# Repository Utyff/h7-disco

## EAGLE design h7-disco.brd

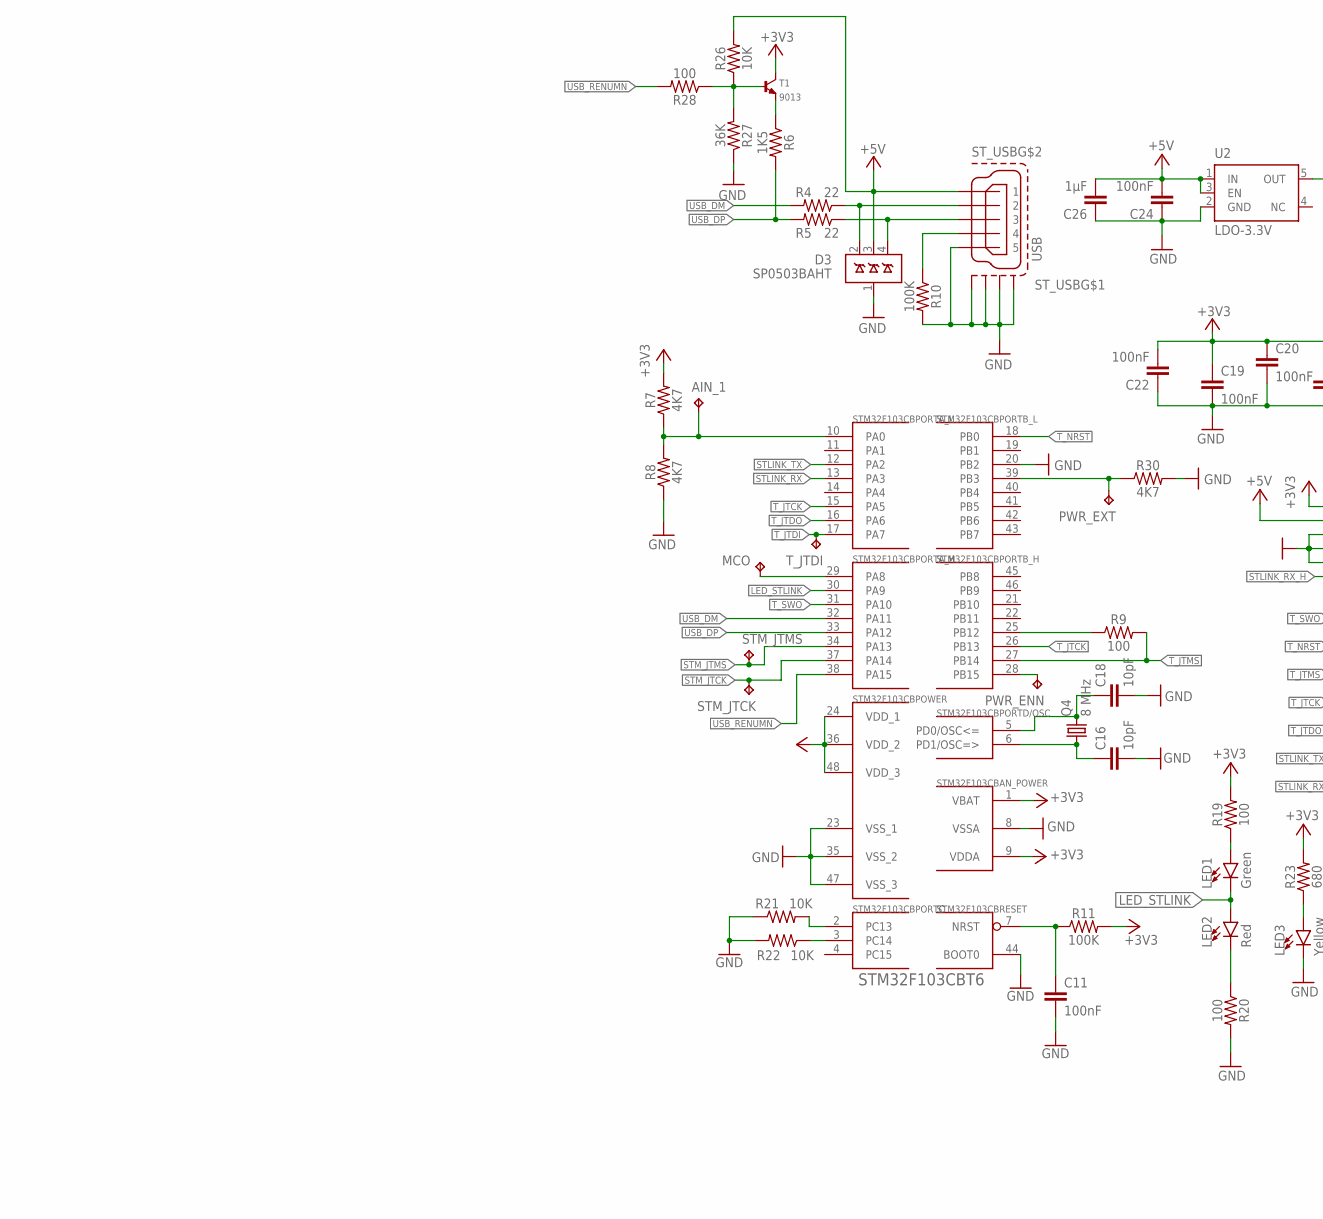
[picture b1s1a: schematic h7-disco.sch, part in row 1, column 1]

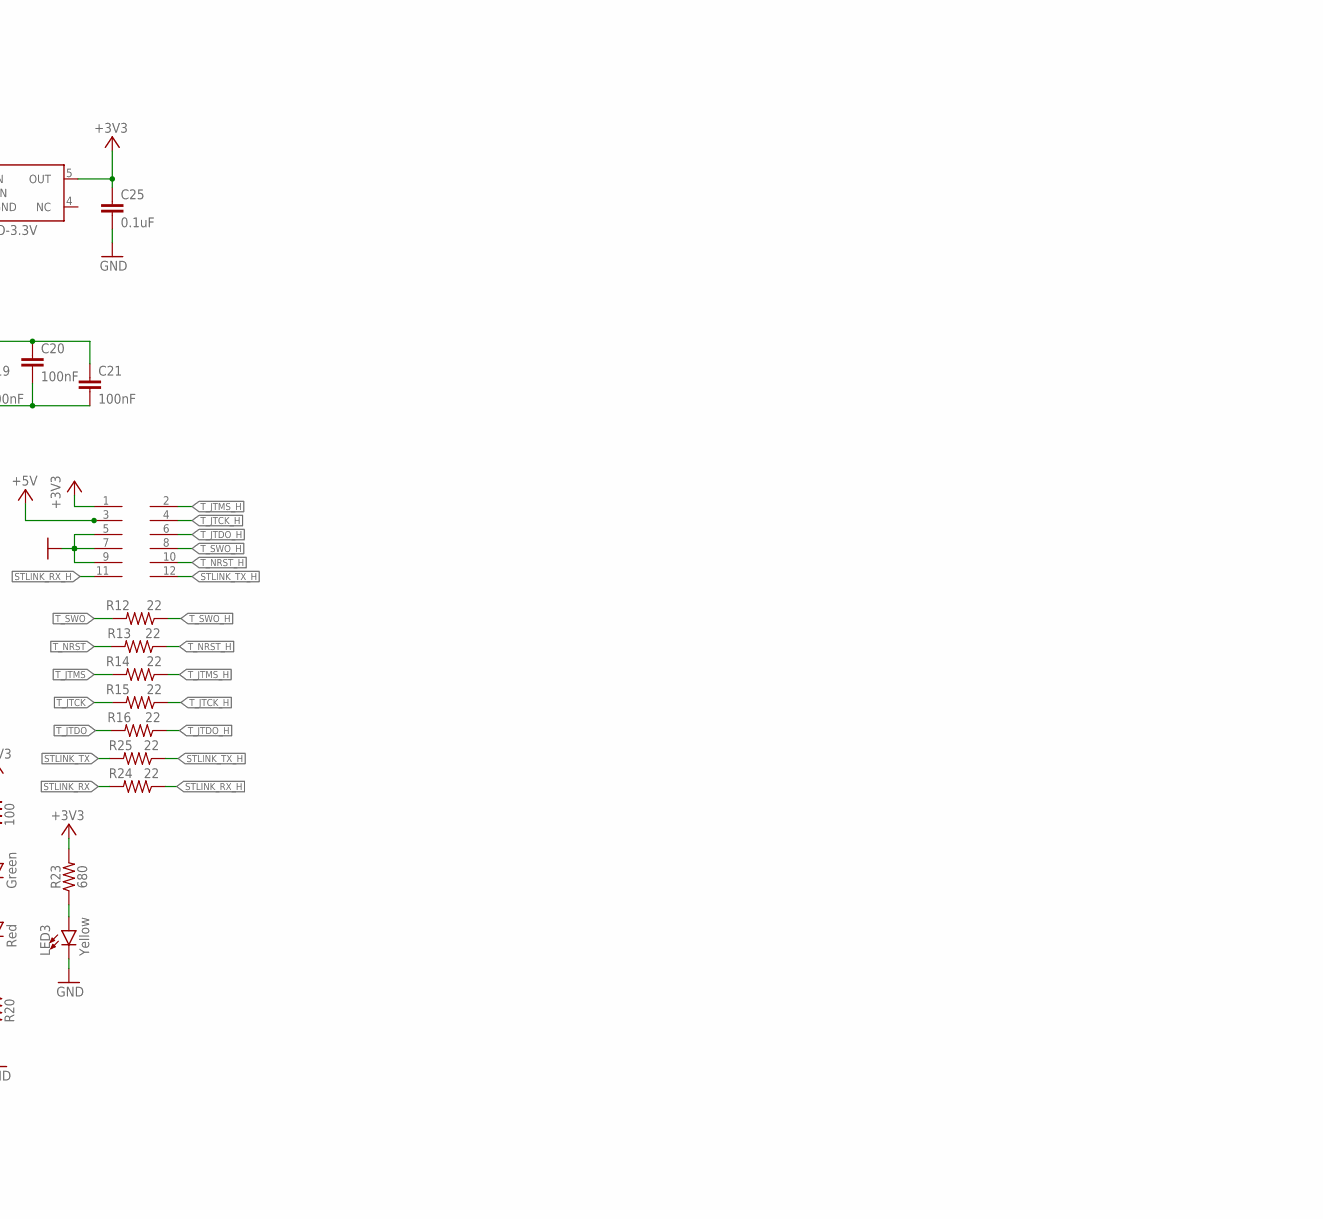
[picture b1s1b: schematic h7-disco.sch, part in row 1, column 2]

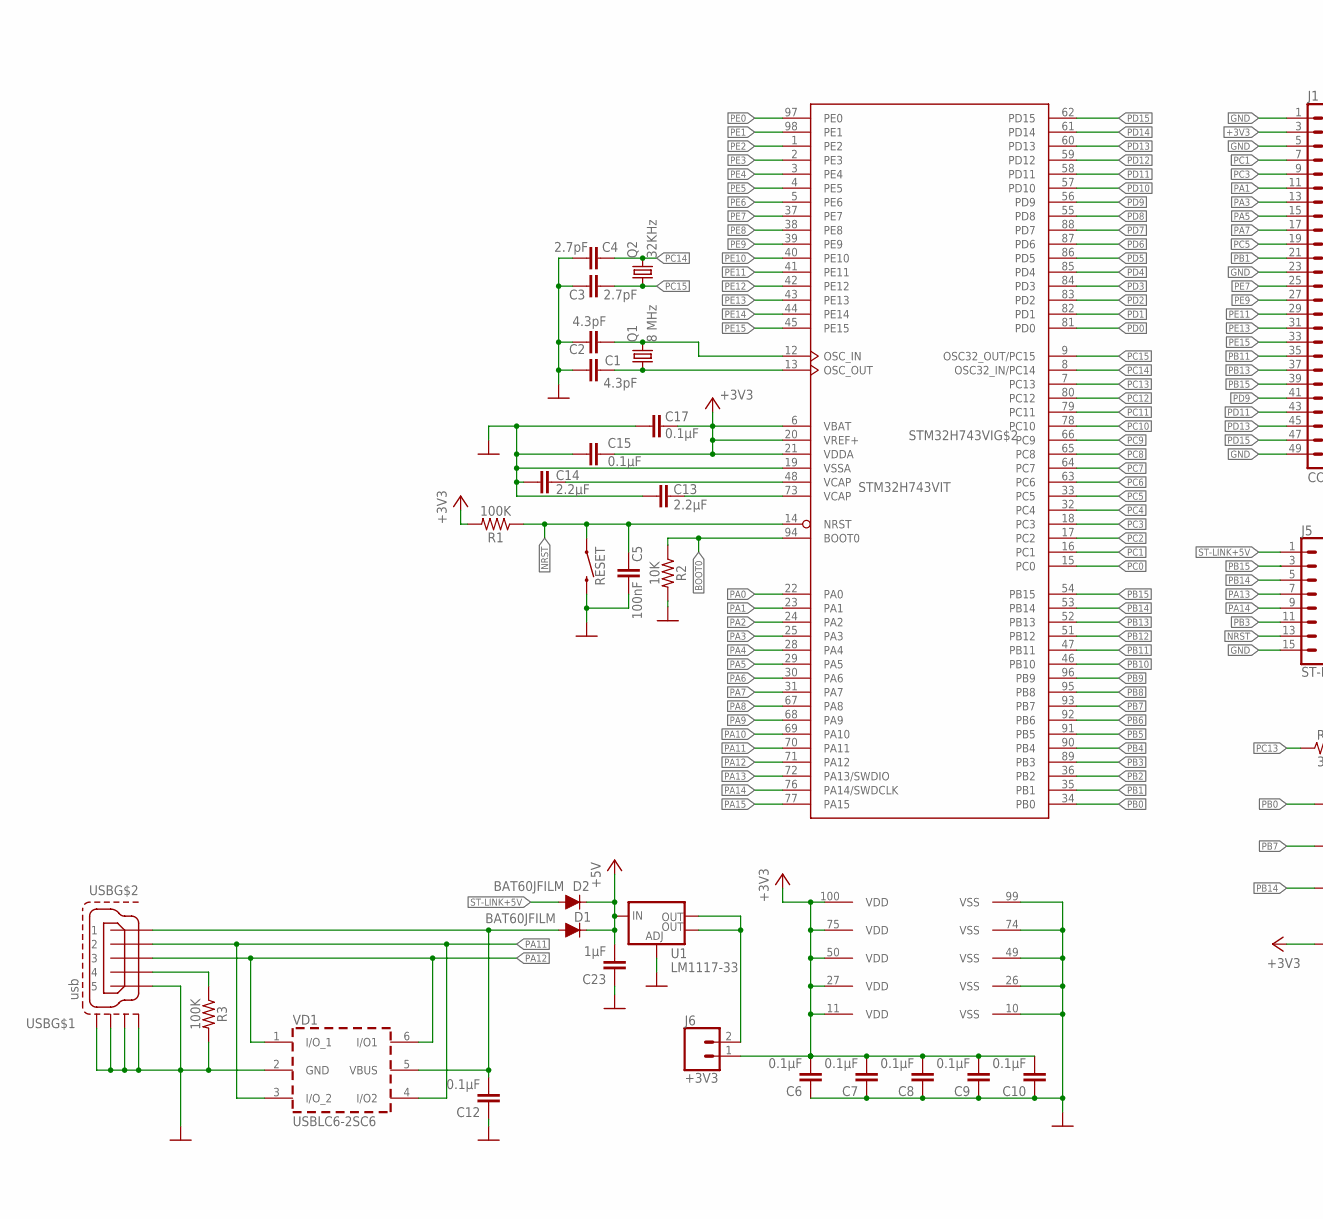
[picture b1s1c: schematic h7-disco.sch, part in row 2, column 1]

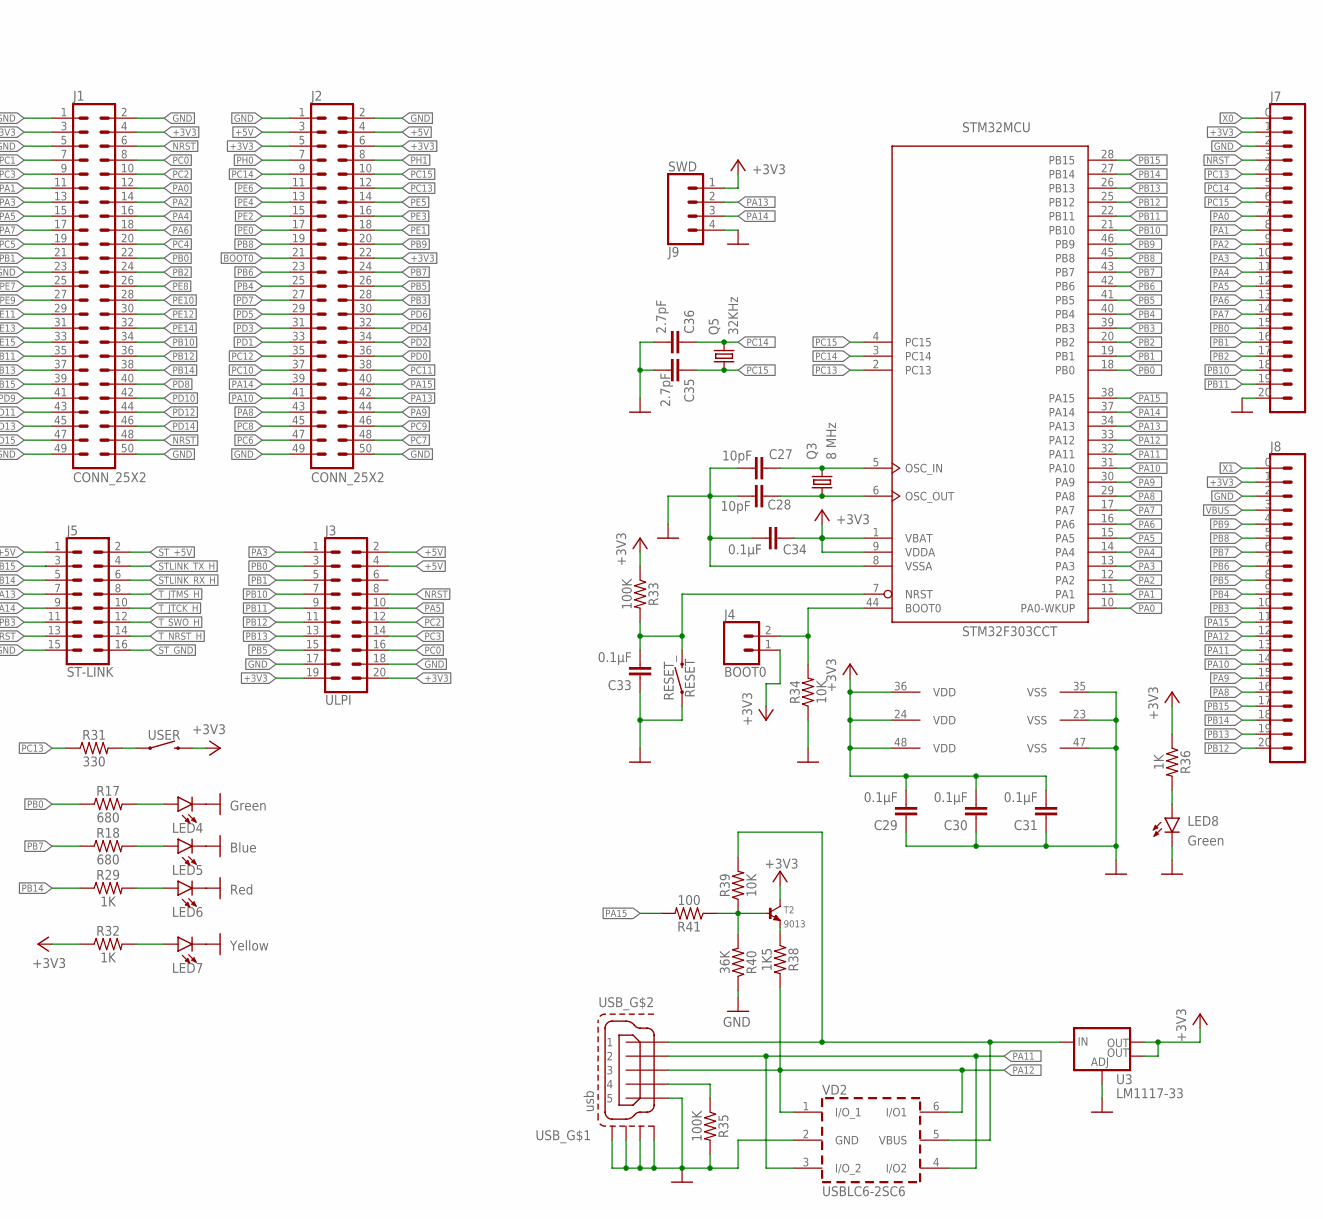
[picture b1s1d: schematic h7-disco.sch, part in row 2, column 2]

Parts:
AIN_1: TPTP10R; TP10R
C1, C2: 4.3pF; 0805
C3, C4, C35, C36: 2.7pF; 0805
C5, C11, C19, C20, C21, C22, C24: 100nF; 0805
C6, C7, C8, C9, C10, C12, C15, C17, C29, C30, C31, C33, C34: 0.1µF; 0805
C13, C14: 2.2µF; 0805
C16, C18, C27, C28: 10pF; 0805
C23, C26: 1µF; 1206
C25: 0.1uF; 0805
CN2: M06X2; PLANAR-6X2
D1, D2: BAT60JFILM; SOD-323
D3: SP0503BAHT; SOT143
J1, J2: CONN_25X2; 2X25
J3: ULPI; 2X10-MIRROR
J4: BOOT0; 1X02
J5: ST-LINK; 2X8
J6: +3V3; 1X02
J7, J8: CONN_21; 1X21
J9: SWD; 1X04
LED1, LED4, LED8: Green; LED-0805
LED2, LED6: Red; LED-0805
LED3, LED7: Yellow; LED-0805
LED5: Blue; LED-0805
MCO: TPTP10R; TP10R
PWR_ENN: TPTP10R; TP10R
PWR_EXT: TPTP10R; TP10R
Q1, Q3, Q4: 8 MHz; HC49/S
Q2, Q5: 32KHz; TC26H
R1, R3, R10, R11, R33, R35: 100K; 0805
R2, R21, R22, R26, R34, R39: 10K; 0805
R4, R5, R12, R13, R14, R15, R16, R24, R25: 22; 0805
R6, R38: 1K5; 0805
R7, R8, R30: 4K7; 0805
R9, R19, R20, R28, R41: 100; 0805
R17, R18, R23: 680; 0805
R27, R40: 36K; 0805
R29, R32, R36: 1K; 0805
R31: 330; 0805
RESET: MOMENTARY-SWITCH-SPST-SMD-6.2MM-TALL; TACTILE_SWITCH_SMD_6.2MM_TALL
RESET_: RESET; TACTILE_SWITCH_SMD_6.0X3.5MM
STM32: STM32F303CCT; LQFP48
STM32F103CB: STM32F103CBT6; TQFP48
STM32H743VI: STM32H743VIT; LQFP100
STM_JTCK: TPTP10R; TP10R
STM_JTMS: TPTP10R; TP10R
ST_USB: USB; MICRO_USB-B_4.85_HORN
T1, T2: 9013; SOT-23
T_JTDI: TPTP10R; TP10R
U1, U3: LM1117-33; SOT223
U2: LDO-3.3V; SOT23-5
USB: usb; MICRO_USB-B_4.85_HORN
USB_: usb; MICRO_USB-B_4.85_HORN
USER: MOMENTARY-SWITCH-SPST-SMD-6.2MM-TALL; TACTILE_SWITCH_SMD_6.2MM_TALL
VD1, VD2: USBLC6-2SC6; SOT-23-6L

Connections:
+3V3: C6.2, C7.2, C8.2, C9.2, C10.2, C15.1, C17.1, C29.2, C30.2, C31.2, C34.1, J1.3, J1.4, J2.5, J2.6, J2.22, J3.19, J3.20, J4.1, J6.1, J7.1, J8.1, J9.1, R1.2, R32.1, R33.1, R36.1, STM32.1 (VBAT), STM32.9 (VDDA), STM32.24 (VDD), STM32.36 (VDD), STM32.48 (VDD), STM32H743VI.6 (VBAT), STM32H743VI.11 (VDD), STM32H743VI.20 (VREF+), STM32H743VI.21 (VDDA), STM32H743VI.27 (VDD), STM32H743VI.50 (VDD), STM32H743VI.75 (VDD), STM32H743VI.100 (VDD), T2.3 (C), U3.2 (OUT), U3.4 (OUT), USER.B2 (2)
+5V: C23.2, D1.C, D2.C, J2.3, J2.4, J3.2, J3.4, U1.3 (IN)
AIN_1: AIN_1.TP, R7.1, R8.2, STM32F103CB.10 (PA0)
BOOT0: J2.21, R2.1, STM32H743VI.94 (BOOT0)
BOOT0_: J4.2, R34.2, STM32.44 (BOOT0)
D+1: D3.4 (D3), R5.1, ST_USB.3
D-1: D3.2 (D1), R4.1, ST_USB.2
GND: C1.1, C2.1, C3.1, C4.1, C5.1, C6.1, C7.1, C8.1, C9.1, C10.1, C12.1, C13.2, C14.2, C15.2, C17.2, C23.1, C27.1, C28.2, C29.1, C30.1, C31.1, C33.1, C34.2, C35.1, C36.1, J1.1, J1.2, J1.5, J1.23, J1.49, J1.50, J2.1, J2.2, J2.49, J2.50, J3.17, J3.18, J5.15, J7.2, J7.20, J8.2, J9.4, LED4.C, LED5.C, LED6.C, LED7.C, LED8.C, R2.2, R3.2, R34.1, R35.2, R40.1, RESET.B2 (2), RESET_.1, STM32.8 (VSSA), STM32.23 (VSS), STM32.35 (VSS), STM32.47 (VSS), STM32H743VI.10 (VSS), STM32H743VI.19 (VSSA), STM32H743VI.26 (VSS), STM32H743VI.49 (VSS), STM32H743VI.74 (VSS), STM32H743VI.99 (VSS), U1.1 (ADJ), U3.1 (ADJ), USB.5, USB.M1 (S1), USB.M2 (S2), USB.M3 (S3), USB.M4 (S4), USB_.5, USB_.M1 (S1), USB_.M2 (S2), USB_.M3 (S3), USB_.M4 (S4), VD1.2 (GND), VD2.2 (GND)
ID: R3.1, USB.4
ID_: R35.1, USB_.4
LED_STLINK: LED1.C, LED2.A, STM32F103CB.30 (PA9)
MCO: MCO.TP, STM32F103CB.29 (PA8)
unnamed: C1.2, Q1.1, STM32H743VI.13 (OSC_OUT)
unnamed: C2.2, Q1.2, STM32H743VI.12 (OSC_IN)
unnamed: C11.1, R11.1, STM32F103CB.7 (NRST)
unnamed: C18.1, Q4.2, STM32F103CB.5 (PD0/OSC<=)
unnamed: C16.1, Q4.1, STM32F103CB.6 (PD1/OSC=>)
unnamed: R26.1, R27.2, R28.1, T1.1 (B)
unnamed: LED2.C, R20.1
unnamed: LED1.A, R19.1
unnamed: LED5.A, R18.2
unnamed: J6.2, U1.2 (OUT), U1.4 (OUT)
unnamed: LED3.A, R23.1
unnamed: R6.1, T1.2 (E)
unnamed: LED4.A, R17.2
unnamed: R21.2, STM32F103CB.2 (PC13)
unnamed: R22.1, STM32F103CB.3 (PC14)
unnamed: LED7.A, R32.2
unnamed: R10.1, ST_USB.4
unnamed: R38.1, T2.2 (E)
unnamed: R39.1, R40.2, R41.1, T2.1 (B)
unnamed: LED6.A, R29.2
unnamed: R31.2, USER.A2 (1)
unnamed: LED8.A, R36.2
NRST: C5.2, J1.6, J1.48, J3.8, J5.13, R1.1, RESET.A2 (1), STM32H743VI.14 (NRST)
NRST_: C33.2, J7.3, R33.2, RESET_.2, STM32.7 (NRST)
PA0: J1.12, STM32H743VI.22 (PA0)
PA0_: J7.7, STM32.10 (PA0-WKUP)
PA1: J1.11, STM32H743VI.23 (PA1)
PA1_: J7.8, STM32.11 (PA1)
PA2: J1.14, STM32H743VI.24 (PA2)
PA2_: J7.9, STM32.12 (PA2)
PA3: J1.13, J3.1, STM32H743VI.25 (PA3)
PA3_: J7.10, STM32.13 (PA3)
PA4: J1.16, STM32H743VI.28 (PA4)
PA4_: J7.11, STM32.14 (PA4)
PA5: J1.15, J3.10, STM32H743VI.29 (PA5)
PA5_: J7.12, STM32.15 (PA5)
PA6: J1.18, STM32H743VI.30 (PA6)
PA6_: J7.13, STM32.16 (PA6)
PA7: J1.17, STM32H743VI.31 (PA7)
PA7_: J7.14, STM32.17 (PA7)
PA8: J2.43, STM32H743VI.67 (PA8)
PA8_: J8.16, STM32.29 (PA8)
PA9: J2.44, STM32H743VI.68 (PA9)
PA9_: J8.15, STM32.30 (PA9)
PA10: J2.41, STM32H743VI.69 (PA10)
PA10_: J8.14, STM32.31 (PA10)
PA11: STM32H743VI.70 (PA11), USB.2, VD1.3 (I/O_2), VD1.4 (I/O2)
PA11_: J8.13, STM32.32 (PA11), USB_.2, VD2.3 (I/O_2), VD2.4 (I/O2)
PA12: STM32H743VI.71 (PA12), USB.3, VD1.1 (I/O_1), VD1.6 (I/O1)
PA12_: J8.12, R38.2, STM32.33 (PA12), USB_.3, VD2.1 (I/O_1), VD2.6 (I/O1)
PA13: J2.42, J5.7, STM32H743VI.72 (PA13/SWDIO)
PA13_: J9.2, STM32.34 (PA13)
PA14: J2.39, J5.9, STM32H743VI.76 (PA14/SWDCLK)
PA14_: J9.3, STM32.37 (PA14)
PA15: J2.40, STM32H743VI.77 (PA15)
PA15_: J8.11, R41.2, STM32.38 (PA15)
PB0: J1.22, J3.3, R17.1, STM32H743VI.34 (PB0)
PB0_: J7.15, STM32.18 (PB0)
PB1: J1.21, J3.5, STM32H743VI.35 (PB1)
PB1_: J7.16, STM32.19 (PB1)
PB2: J1.24, STM32H743VI.36 (PB2)
PB2_: J7.17, STM32.20 (PB2)
PB3: J2.28, J5.11, STM32H743VI.89 (PB3)
PB3_: J8.10, STM32.39 (PB3)
PB4: J2.25, STM32H743VI.90 (PB4)
PB4_: J8.9, STM32.40 (PB4)
PB5: J2.26, J3.15, STM32H743VI.91 (PB5)
PB5_: J8.8, STM32.41 (PB5)
PB6: J2.23, STM32H743VI.92 (PB6)
PB6_: J8.7, STM32.42 (PB6)
PB7: J2.24, R18.1, STM32H743VI.93 (PB7)
PB7_: J8.6, STM32.43 (PB7)
PB8: J2.19, STM32H743VI.95 (PB8)
PB8_: J8.5, STM32.45 (PB8)
PB9: J2.20, STM32H743VI.96 (PB9)
PB9_: J8.4, STM32.46 (PB9)
PB10: J1.34, J3.7, STM32H743VI.46 (PB10)
PB10_: J7.18, STM32.21 (PB10)
PB11: J1.35, J3.9, STM32H743VI.47 (PB11)
PB11_: J7.19, STM32.22 (PB11)
PB12: J1.36, J3.11, STM32H743VI.51 (PB12)
PB12_: J8.20, STM32.25 (PB12)
PB13: J1.37, J3.13, STM32H743VI.52 (PB13)
PB13_: J8.19, STM32.26 (PB13)
PB14: J1.38, J5.5, R29.1, STM32H743VI.53 (PB14)
PB14_: J8.18, STM32.27 (PB14)
PB15: J1.39, J5.3, STM32H743VI.54 (PB15)
PB15_: J8.17, STM32.28 (PB15)
PB16: PWR_ENN.TP, STM32F103CB.28 (PB15)
PC0: J1.8, J3.16, STM32H743VI.15 (PC0)
PC1: J1.7, STM32H743VI.16 (PC1)
PC2: J1.10, J3.12, STM32H743VI.17 (PC2)
PC3: J1.9, J3.14, STM32H743VI.18 (PC3)
PC4: J1.20, STM32H743VI.32 (PC4)
PC5: J1.19, STM32H743VI.33 (PC5)
PC6: J2.47, STM32H743VI.63 (PC6)
PC7: J2.48, STM32H743VI.64 (PC7)
PC8: J2.45, STM32H743VI.65 (PC8)
PC9: J2.46, STM32H743VI.66 (PC9)
PC10: J2.37, STM32H743VI.78 (PC10)
PC11: J2.38, STM32H743VI.79 (PC11)
PC12: J2.35, STM32H743VI.80 (PC12)
PC13: J2.12, R31.1, STM32H743VI.7 (PC13)
PC13_: J7.4, STM32.2 (PC13)
PC14: C4.2, J2.9, Q2.2, STM32H743VI.8 (OSC32_IN/PC14)
PC14_: C36.2, J7.5, Q5.2, STM32.3 (PC14)
PC15: C3.2, J2.10, Q2.1, STM32H743VI.9 (OSC32_OUT/PC15)
PC15_: C35.2, J7.6, Q5.1, STM32.4 (PC15)
PD0: J2.36, STM32H743VI.81 (PD0)
PD1: J2.33, STM32H743VI.82 (PD1)
PD2: J2.34, STM32H743VI.83 (PD2)
PD3: J2.31, STM32H743VI.84 (PD3)
PD4: J2.32, STM32H743VI.85 (PD4)
PD5: J2.29, STM32H743VI.86 (PD5)
PD6: J2.30, STM32H743VI.87 (PD6)
PD7: J2.27, STM32H743VI.88 (PD7)
PD8: J1.40, STM32H743VI.55 (PD8)
PD9: J1.41, STM32H743VI.56 (PD9)
PD10: J1.42, STM32H743VI.57 (PD10)
PD11: J1.43, STM32H743VI.58 (PD11)
PD12: J1.44, STM32H743VI.59 (PD12)
PD13: J1.45, STM32H743VI.60 (PD13)
PD14: J1.46, STM32H743VI.61 (PD14)
PD15: J1.47, STM32H743VI.62 (PD15)
PE0: J2.17, STM32H743VI.97 (PE0)
PE1: J2.18, STM32H743VI.98 (PE1)
PE2: J2.15, STM32H743VI.1 (PE2)
PE3: J2.16, STM32H743VI.2 (PE3)
PE4: J2.13, STM32H743VI.3 (PE4)
PE5: J2.14, STM32H743VI.4 (PE5)
PE6: J2.11, STM32H743VI.5 (PE6)
PE7: J1.25, STM32H743VI.37 (PE7)
PE8: J1.26, STM32H743VI.38 (PE8)
PE9: J1.27, STM32H743VI.39 (PE9)
PE10: J1.28, STM32H743VI.40 (PE10)
PE11: J1.29, STM32H743VI.41 (PE11)
PE12: J1.30, STM32H743VI.42 (PE12)
PE13: J1.31, STM32H743VI.43 (PE13)
PE14: J1.32, STM32H743VI.44 (PE14)
PE15: J1.33, STM32H743VI.45 (PE15)
PF0_: C27.2, Q3.2, STM32.5 (OSC_IN)
PF1_: C28.1, Q3.1, STM32.6 (OSC_OUT)
PH0: J2.7
PH1: J2.8
PWR_EXT: PWR_EXT.TP, R30.1, STM32F103CB.39 (PB3)
ST-LINK+5V: D2.A, J5.1
STLINK_RX: R24.2, STM32F103CB.13 (PA3)
STLINK_RX_H: CN2.11, J5.6, R24.1
STLINK_TX: R25.2, STM32F103CB.12 (PA2)
STLINK_TX_H: CN2.12, J5.4, R25.1
STM_JTCK: STM32F103CB.37 (PA14), STM_JTCK.TP
STM_JTMS: STM32F103CB.34 (PA13), STM_JTMS.TP
ST_+3V3: C19.1, C20.1, C21.1, C22.2, C25.1, CN2.1, R7.2, R11.2, R19.2, R23.2, STM32F103CB.1 (VBAT), STM32F103CB.9 (VDDA), STM32F103CB.24 (VDD_1), STM32F103CB.36 (VDD_2), STM32F103CB.48 (VDD_3), T1.3 (C), U2.5 (OUT)
ST_+5V: C24.2, C26.2, CN2.3, D3.3 (D2), J5.2, R26.2, ST_USB.1, U2.1 (IN), U2.3 (EN)
ST_GND: C11.2, C16.2, C18.2, C19.2, C20.2, C21.2, C22.1, C24.1, C25.2, C26.1, CN2.5, CN2.7, CN2.9, D3.1 (GND), J5.16, LED3.C, R8.1, R10.2, R20.2, R21.1, R22.2, R27.1, R30.2, STM32F103CB.8 (VSSA), STM32F103CB.20 (PB2), STM32F103CB.23 (VSS_1), STM32F103CB.35 (VSS_2), STM32F103CB.44 (BOOT0), STM32F103CB.47 (VSS_3), ST_USB.5, ST_USB.M1 (S1), ST_USB.M2 (S2), ST_USB.M3 (S3), ST_USB.M4 (S4), U2.2 (GND)
T_JTCK: R15.2, STM32F103CB.15 (PA5), STM32F103CB.26 (PB13)
T_JTCK_H: CN2.4, J5.10, R15.1
T_JTDI: STM32F103CB.17 (PA7), T_JTDI.TP
T_JTDO: R16.2, STM32F103CB.16 (PA6)
T_JTDO_H: CN2.6, R16.1
T_JTMS: R9.2, R14.2, STM32F103CB.27 (PB14)
T_JTMS_H: CN2.2, J5.8, R14.1
T_NRST: R13.2, STM32F103CB.18 (PB0)
T_NRST_H: CN2.10, J5.14, R13.1
T_SWDIO_IN: R9.1, STM32F103CB.25 (PB12)
T_SWO: R12.2, STM32F103CB.31 (PA10)
T_SWO_H: CN2.8, J5.12, R12.1
USB_DM: R4.2, STM32F103CB.32 (PA11)
USB_DP: R5.2, R6.2, STM32F103CB.33 (PA12)
USB_RENUMN: R28.2, STM32F103CB.38 (PA15)
VBUS: C12.2, D1.A, USB.1, VD1.5 (VBUS)
VBUS_: J8.3, R39.2, U3.3 (IN), USB_.1, VD2.5 (VBUS)
VCAP1: C14.1, STM32H743VI.48 (VCAP)
VCAP2: C13.1, STM32H743VI.73 (VCAP)
X0: J7.0
X1: J8.0

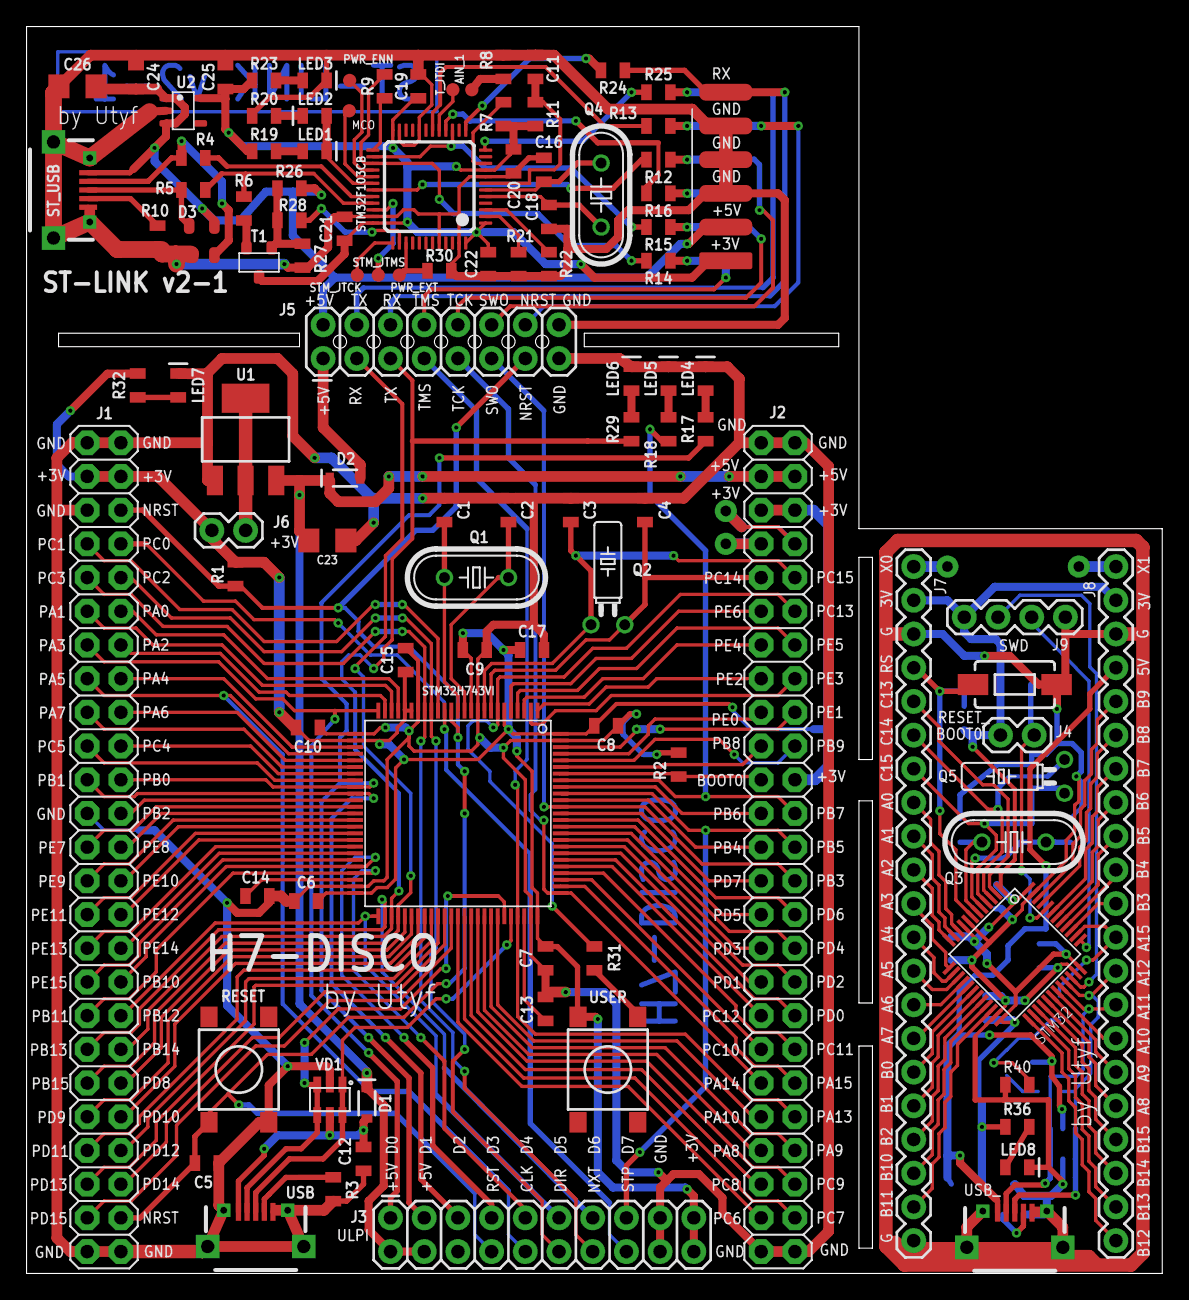
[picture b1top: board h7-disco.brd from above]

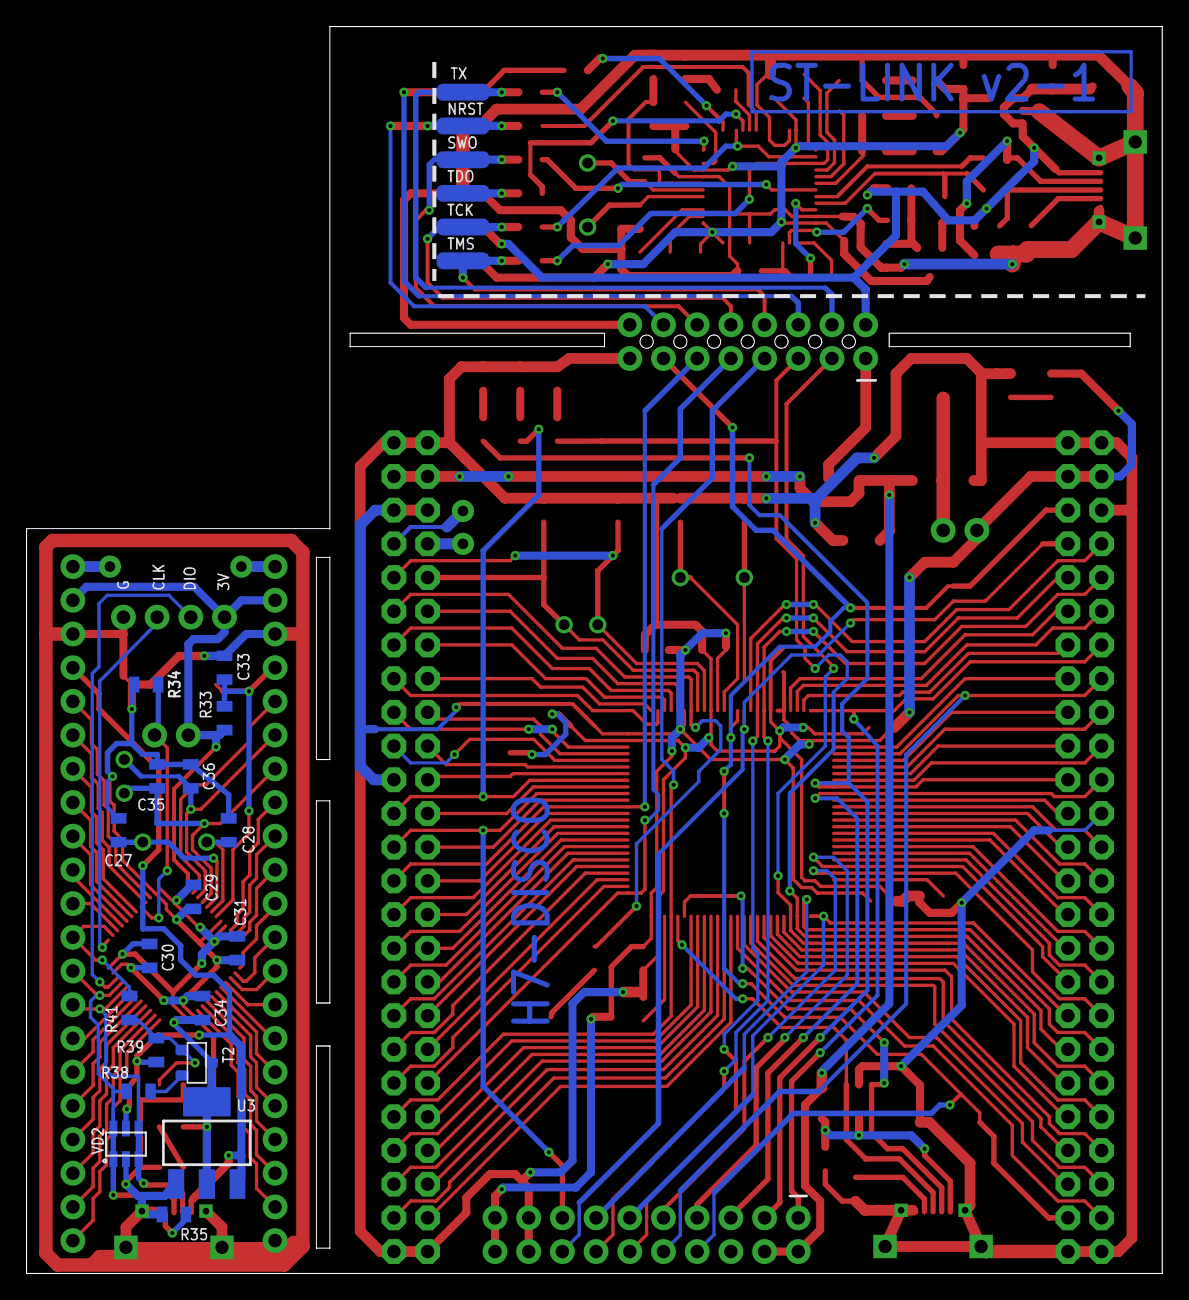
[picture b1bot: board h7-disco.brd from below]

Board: 2 copper layers, 85.6 x 94.0 mm, 124 parts (18 on the bottom side), 184 nets.

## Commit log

2018-02-25 Initial
2018-02-25 add schematics
2018-03-09 Elements value fix.
2018-03-10 add MCO pin
2018-03-11 minor update
2018-03-24 improve

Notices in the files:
parts and their libraries:
SparkFun-Capacitors: Licensing: Creative Commons ShareAlike 4.0 International - https://creativecommons.org/licenses/by-sa/4.0
